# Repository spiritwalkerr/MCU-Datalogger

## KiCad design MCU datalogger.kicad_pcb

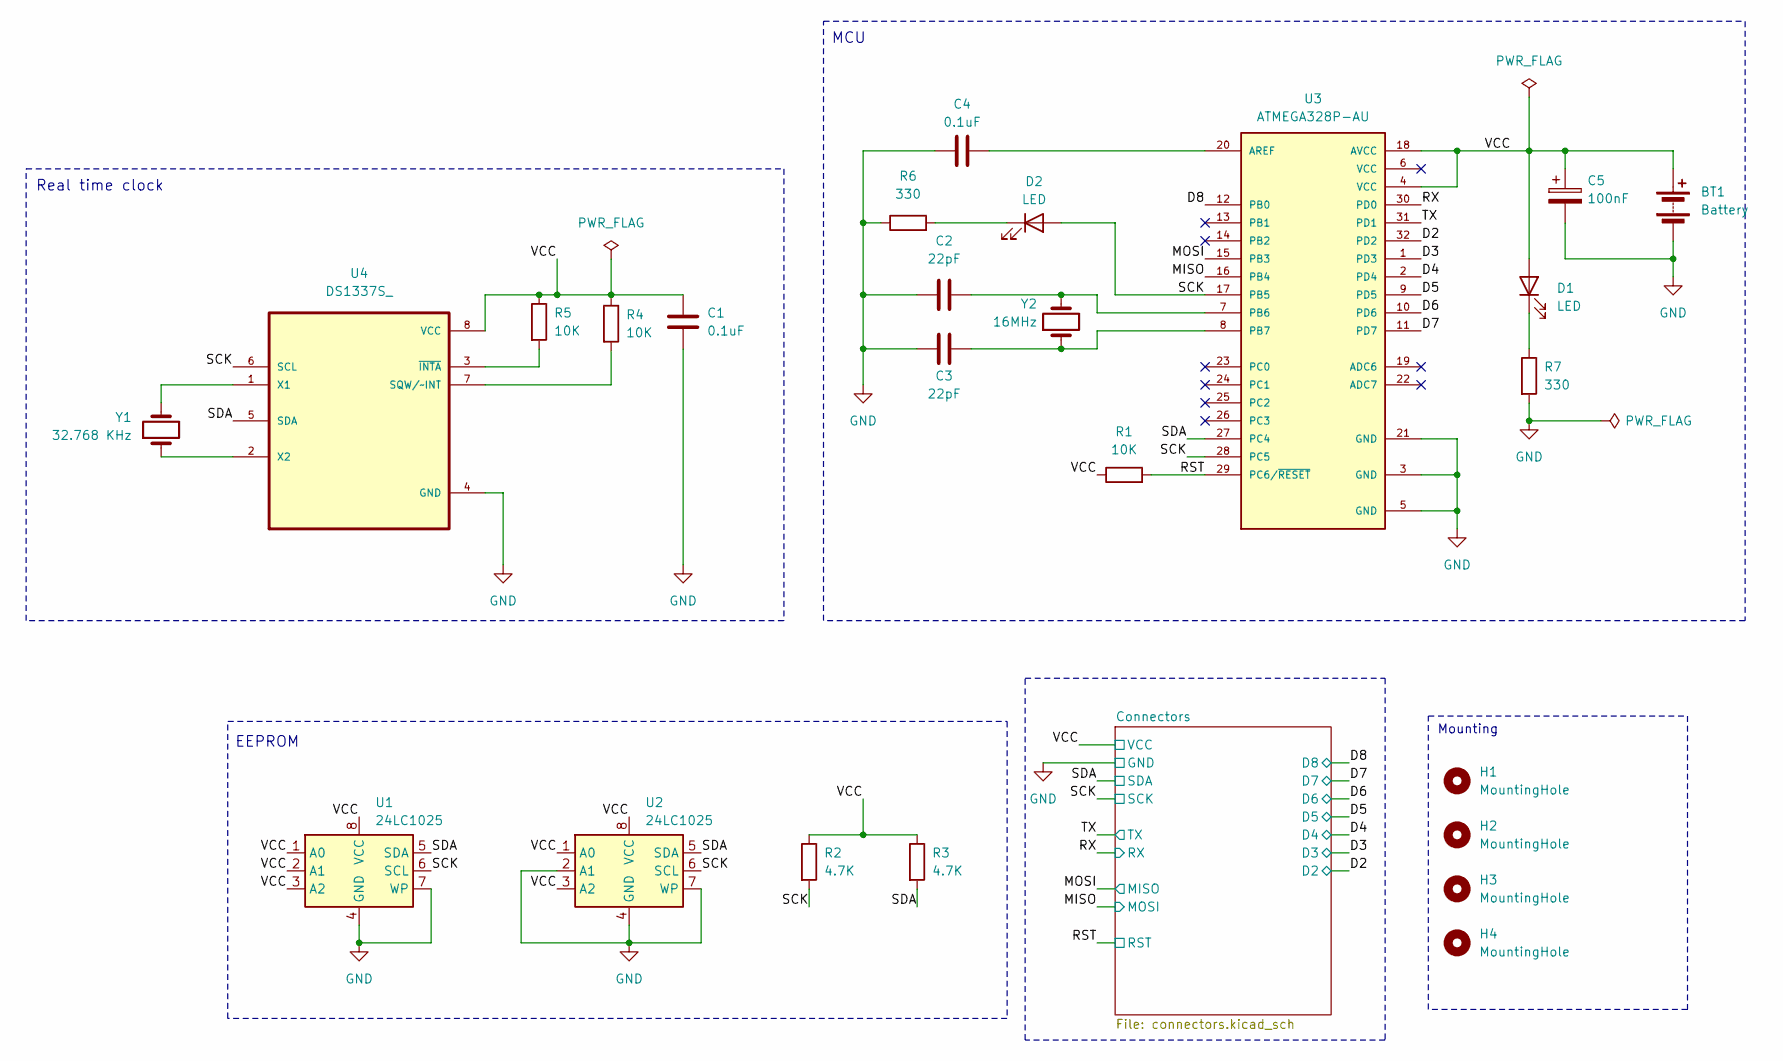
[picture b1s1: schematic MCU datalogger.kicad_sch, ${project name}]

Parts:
BT1: Battery; PinHeader_1x02_P2.54mm_Vertical
C1, C4: 0.1uF; C_0805_2012Metric
C2, C3: 22pF; C_0805_2012Metric
C5: 100nF; C_0805_2012Metric
D1, D2: LED; LED_0805_2012Metric
H1, H2, H3, H4: MountingHole; MountingHole_2.1mm
R1, R4, R5: 10K; R_0805_2012Metric
R2, R3: 4.7K; R_0805_2012Metric
R6, R7: 330; R_0805_2012Metric
U1, U2: 24LC1025; SOIC-8_5.23x5.23mm_P1.27mm
U3: ATMEGA328P-AU; QFP80P900X900X120-32N; PARTREV 8271A
U4: DS1337S_; SOIC127P600X175-8N
Y1: 32.768 KHz; Crystal_SMD_5032-2Pin_5.0x3.2mm_HandSoldering
Y2: 16MHz; Crystal_SMD_5032-2Pin_5.0x3.2mm_HandSoldering

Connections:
/D2: U3.32 (PD2); also elsewhere on the board
/D3: U3.1 (PD3); also elsewhere on the board
/D4: U3.2 (PD4); also elsewhere on the board
/D5: U3.9 (PD5); also elsewhere on the board
/D6: U3.10 (PD6); also elsewhere on the board
/D7: U3.11 (PD7); also elsewhere on the board
/D8: U3.12 (PB0); also elsewhere on the board
/MISO: U3.16 (PB4); also elsewhere on the board
/MOSI: U3.15 (PB3); also elsewhere on the board
/RST: R1.2, U3.29 (PC6/~RESET); also elsewhere on the board
/RX: U3.30 (PD0); also elsewhere on the board
/SCK: D2.2 (A), R2.2, U1.6 (SCL), U2.6 (SCL), U3.17 (PB5), U3.28 (PC5), U4.6 (SCL); also elsewhere on the board
/SDA: R3.2, U1.5 (SDA), U2.5 (SDA), U3.27 (PC4), U4.5 (SDA); also elsewhere on the board
/TX: U3.31 (PD1); also elsewhere on the board
/VCC: BT1.1 (+), C1.1, C5.1, D1.2 (A), R1.1, R2.1, R3.1, R4.1, R5.1, U1.1 (A0), U1.2 (A1), U1.3 (A2), U1.8 (VCC), U2.1 (A0), U2.3 (A2), U2.8 (VCC), U3.4 (VCC), U3.18 (AVCC), U4.8 (VCC); also elsewhere on the board
GND: BT1.2 (-), C1.2, C2.1, C3.1, C4.1, C5.2, R6.1, R7.2, U1.4 (GND), U1.7 (WP), U2.2 (A1), U2.4 (GND), U2.7 (WP), U3.3 (GND), U3.5 (GND), U3.21 (GND), U4.4 (GND); also elsewhere on the board
unnamed: D1.1 (K), R7.1
unnamed: D2.1 (K), R6.2
unnamed: C4.2, U3.20 (AREF)
unnamed: C2.2, U3.7 (PB6), Y2.2
unnamed: C3.2, U3.8 (PB7), Y2.1
unnamed: R4.2, U4.7 (SQW/~INT)
unnamed: U4.1 (X1), Y1.2
unnamed: U4.2 (X2), Y1.1
unnamed: R5.2, U4.3 (~INTA)

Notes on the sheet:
Real time clock
Mounting
MCU
EEPROM

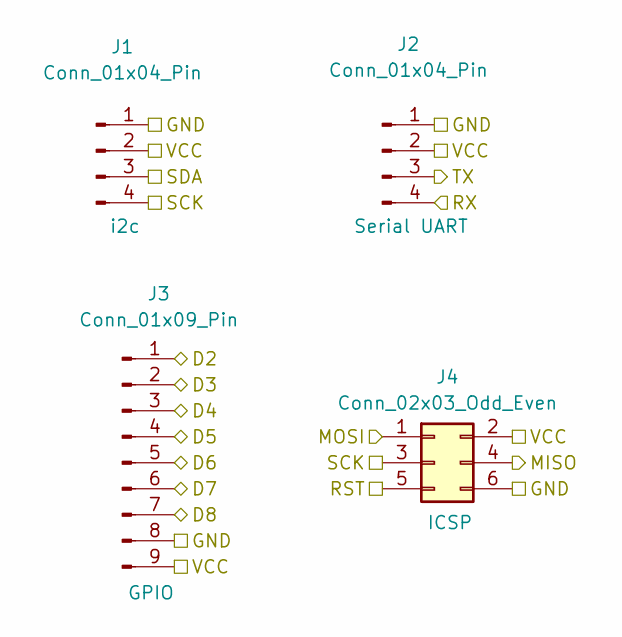
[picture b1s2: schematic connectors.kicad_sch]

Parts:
J1, J2: Conn_01x04_Pin; PinHeader_1x04_P2.54mm_Vertical
J3: Conn_01x09_Pin; PinHeader_1x09_P2.54mm_Vertical
J4: Conn_02x03_Odd_Even; PinHeader_2x03_P2.54mm_Vertical

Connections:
/D2: J3.1; also elsewhere on the board
/D3: J3.2; also elsewhere on the board
/D4: J3.3; also elsewhere on the board
/D5: J3.4; also elsewhere on the board
/D6: J3.5; also elsewhere on the board
/D7: J3.6; also elsewhere on the board
/D8: J3.7; also elsewhere on the board
/MISO: J4.1; also elsewhere on the board
/MOSI: J4.4; also elsewhere on the board
/RST: J4.5; also elsewhere on the board
/RX: J2.4; also elsewhere on the board
/SCK: J1.4, J4.3; also elsewhere on the board
/SDA: J1.3; also elsewhere on the board
/TX: J2.3; also elsewhere on the board
/VCC: J1.2, J2.2, J3.9, J4.2; also elsewhere on the board
GND: J1.1, J2.1, J3.8, J4.6; also elsewhere on the board

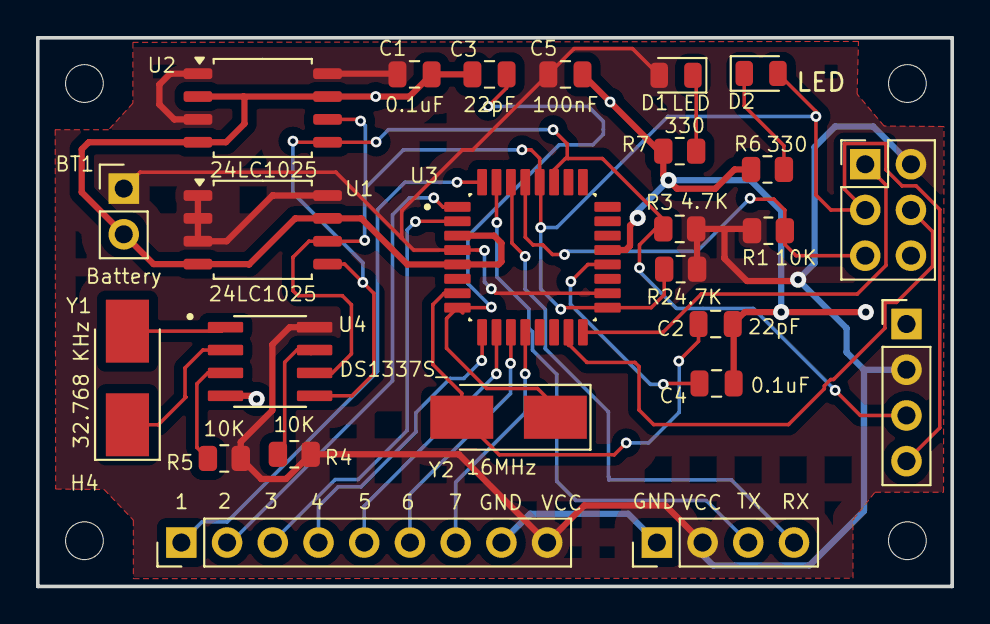
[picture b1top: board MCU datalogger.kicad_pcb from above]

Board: 2 copper layers, 50.8 x 30.5 mm, 29 parts (0 on the bottom side), 25 nets.

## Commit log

2025-02-27 First commit of new project
2025-02-27 setup of EEschema for new project.
2025-02-27 add the symbols
2025-02-27 arranged the symbols
2025-02-27 value of the compents are added
2025-02-27 completed footprint association
2025-02-27 Wires and connected
2025-02-28 Completed the wiring including second sheet
2025-02-28 allocated net classes
2025-02-28 Completed comments
2025-02-28 Setup pcbnew
2025-02-28 complete placement of footprints
2025-03-01 routing expect gnd and vcc
2025-03-06 routing complete
2025-03-06 fixing silkscreen
2025-03-06 fixed thermal relif error by making it solid
2025-03-06 added kicad logo
2025-03-07 kicad logo
2025-03-08 completed project - two layer
2025-03-11 i don't know
2025-03-11 added gitattributes file to ignore PCB files during merge
2025-03-11 made a small change to schema
2025-03-11 added gitattributs file to prevent PCB files from merge
2025-03-12 Fixed two defects in schematic.
